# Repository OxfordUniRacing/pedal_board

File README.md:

# Pedal Board Firmware

Work in progress

## Overview

Every 10ms take readings of each sensor and send a message of the raw readings on the CAN bus.  
Each reading is an average of 256 adc samples.  

## CAN messages

Send:

- Sensor readings (id & format TBD)

Receive:

None

## Bugs

- Sampling frequency is wrong  

## Todo

- CAN network congestion back-off
- Safe mode

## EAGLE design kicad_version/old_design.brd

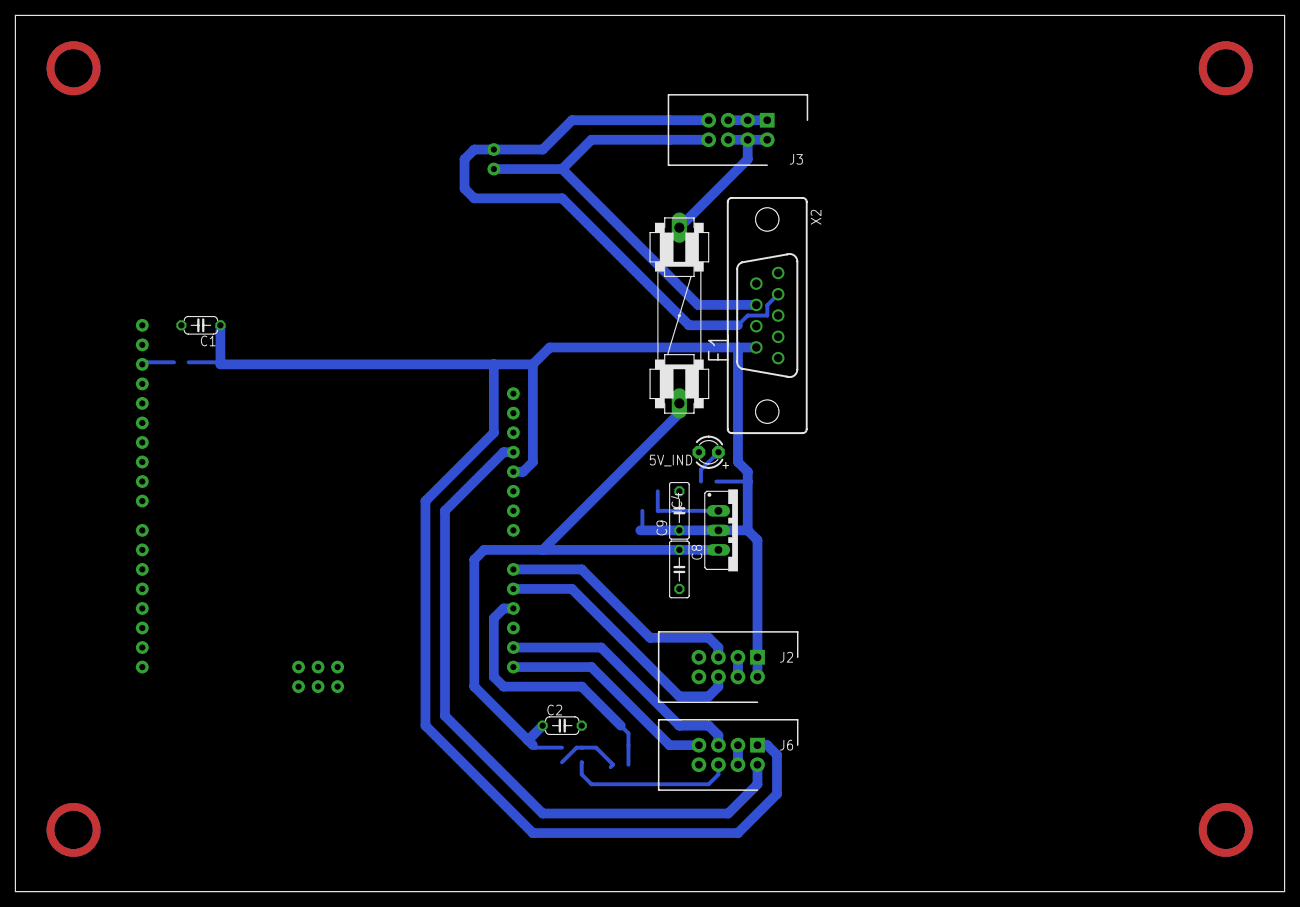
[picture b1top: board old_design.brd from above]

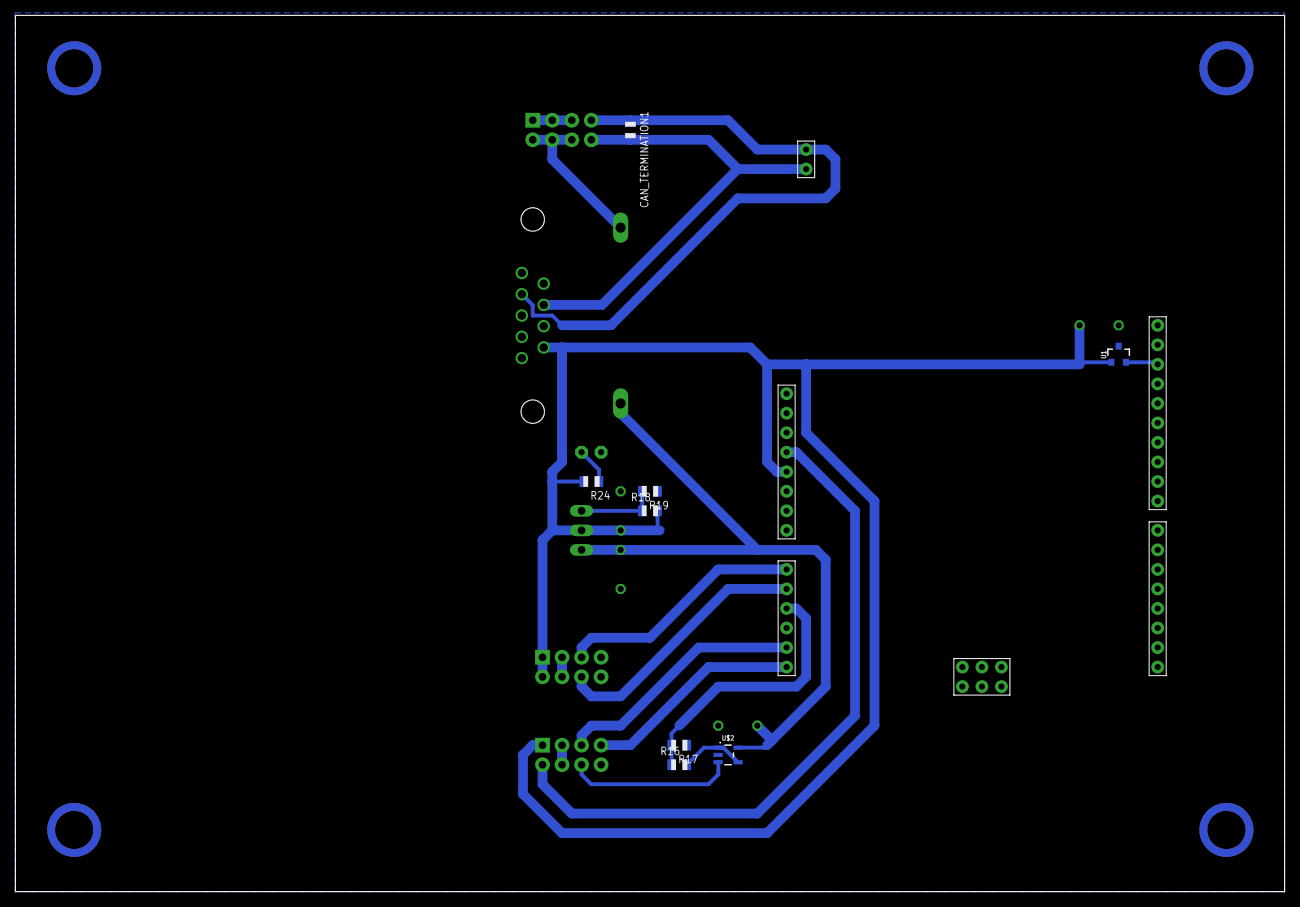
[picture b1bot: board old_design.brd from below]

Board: 2 copper layers, 165.1 x 114.0 mm, 20 parts (9 on the bottom side), 17 nets.

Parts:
5V_IND: LED3MM
C1: 0.47uF; C050-024X044
C2: 0.1uF; C050-024X044
C8: 0.1uF; C050-025X075
C9: 1uF; C050-025X075
CAN_TERMINATION1: 120; R0805
F1: 1A; FUSE
IC4: 317TS
J2: THR_1_2; HDRV8W64P254_2X4_1778X895X915P
J3: PWR_CAN; HDRV8W64P254_2X4_1778X895X915P
J6: BR_POS_PRESS_STWH; HDRV8W64P254_2X4_1778X895X915P
R16, R18: 240; R0805
R17: 1K; R0805
R19: 723; R0805
R24: 1.8K; R0805
U1: REF3040AIDBZT; SOT23-3
U$1: SAMC21-XPLAINED-PRO_NO_EXT1&2&3
U$2: TLV170IDBVR; SOT23-5
X2: D-SUB9-H2M09ST; H2M09ST

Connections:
3.3V: J6.2, U$1.J802-3
5V: C1.1, C9.1, IC4.2, J2.1, J2.2, J6.1, R18.2, R24.2, U1.1, U$1.J802-4, X2.9
12V: C2.1, C8.1, F1.2, IC4.3, U$2.5
12V_BATTERY: F1.1, J3.2, J3.4, J3.6
BR_POSS_1: J6.5, U$1.J803-4
BR_PRESS: R16.1, R17.2, U$1.J803-2
CANH: CAN_TERMINATION1.2, J3.8, U$1.CAN-0, X2.7
CANL: CAN_TERMINATION1.1, J3.7, U$1.CAN-1, X2.2
GND: 5V_IND.K, C1.2, C2.2, C8.2, C9.2, J2.3, J2.4, J3.1, J3.3, J3.5, J6.3, J6.4, R17.1, R19.1, U1.3, U$1.J802-5, U$1.J802-6, U$1.J803-3, U$2.2, X2.3, X2.6
unnamed: R16.2, U$2.1, U$2.4
unnamed: 5V_IND.A, R24.1
unnamed: U1.2, U$1.J801-7
unnamed: IC4.1, R18.1, R19.2
unnamed: J6.6, U$2.3
ST_WH_POSS: J6.7, U$1.J803-5
THR1: J2.5, U$1.J803-0
THR2: J2.6, U$1.J803-1

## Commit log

2019-03-05 Initial import
2019-03-05 Add readme
2019-04-02 Quick and dirty first implementation
    Samples adc at regular interval and sends readings in a can packet
2019-04-05 update makefile
2021-11-10 added kicad export of old schematic
2021-11-17 Added rev B design and kicad version of rev A

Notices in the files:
parts and their libraries:
SparkFun-DiscreteSemi: Licensing: Creative Commons ShareAlike 4.0 International - https://creativecommons.org/licenses/by-sa/4.0
